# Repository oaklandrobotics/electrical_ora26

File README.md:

# electrical_ora26
Electrical 2026 for Oakland Robotics

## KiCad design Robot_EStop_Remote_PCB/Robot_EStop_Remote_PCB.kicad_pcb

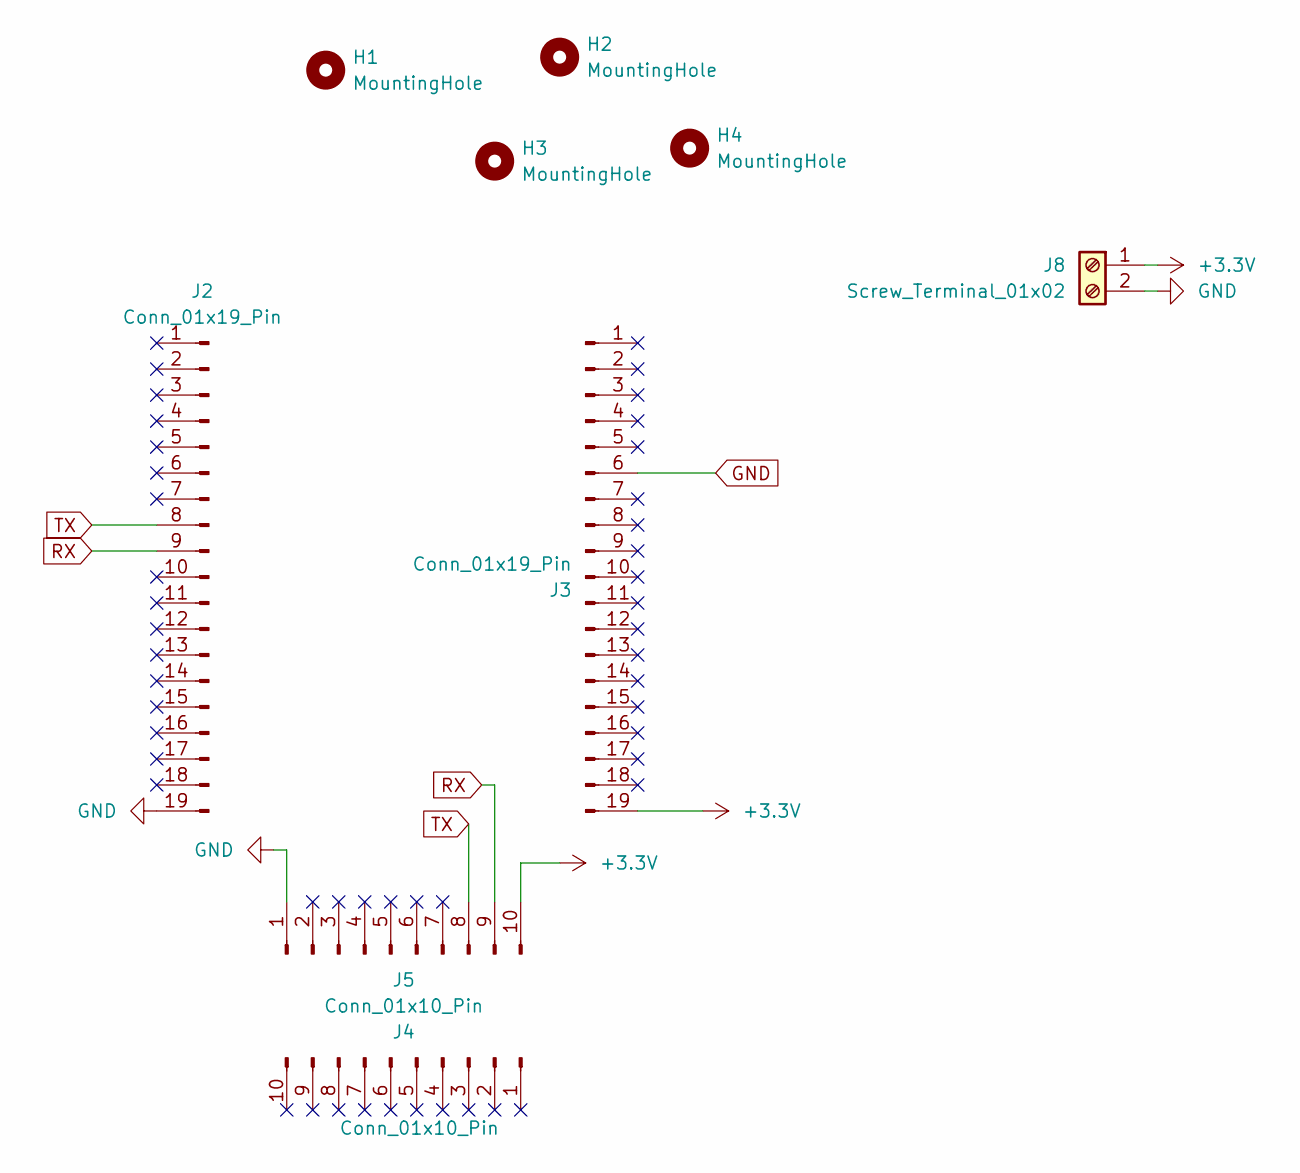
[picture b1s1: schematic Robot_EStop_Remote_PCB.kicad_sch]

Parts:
H1, H2, H3, H4: MountingHole; MountingHole_3.2mm_M3
J2, J3: Conn_01x19_Pin; PinSocket_1x19_P2.54mm_Vertical
J4, J5: Conn_01x10_Pin; PinSocket_1x10_P2.00mm_Vertical
J8: Screw_Terminal_01x02; TerminalBlock_Phoenix_MPT-0,5-2-2.54_1x02_P2.54mm_Horizontal

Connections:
+3.3V: J3.19, J5.10, J8.1
GND: J2.19, J3.6, J5.1, J8.2
RX: J2.9, J5.9
TX: J2.8, J5.8

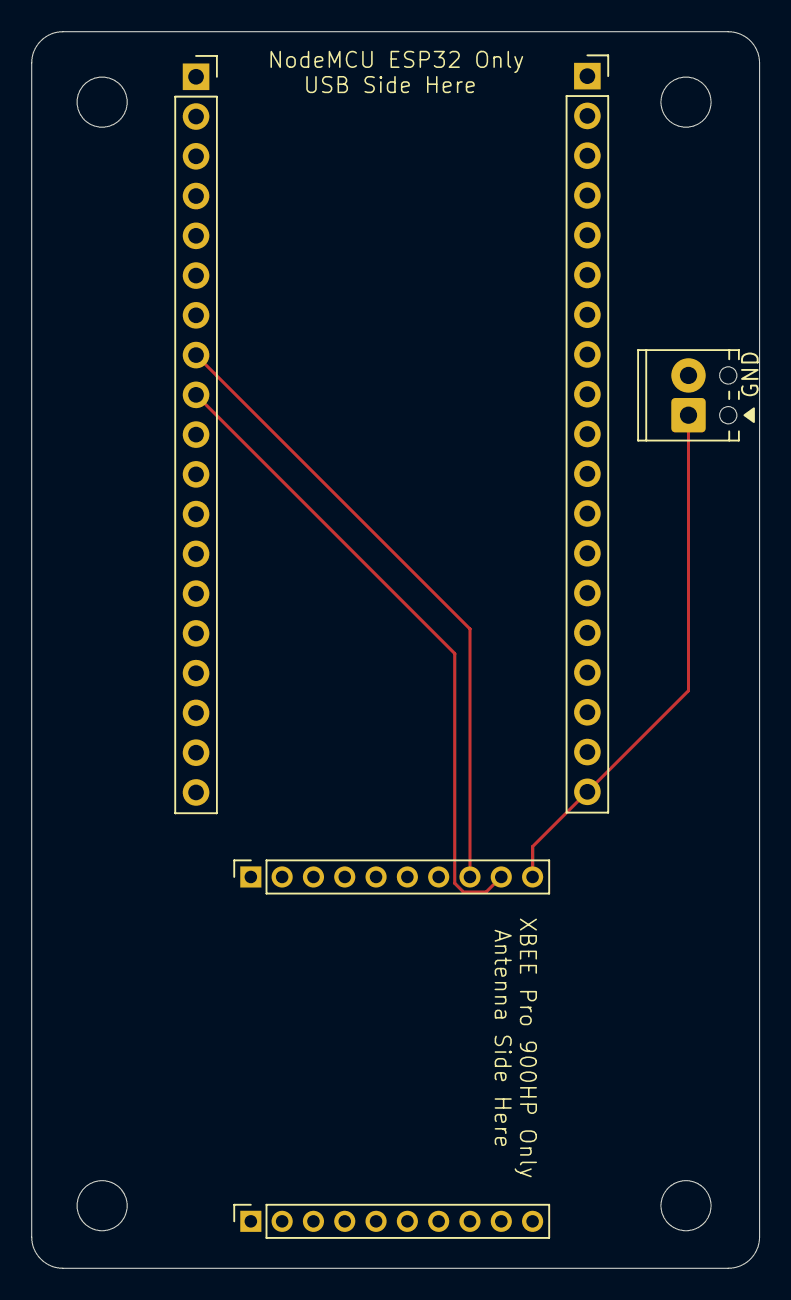
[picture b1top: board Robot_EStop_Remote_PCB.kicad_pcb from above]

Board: 2 copper layers, 46.5 x 79.0 mm, 9 parts (0 on the bottom side), 4 nets.

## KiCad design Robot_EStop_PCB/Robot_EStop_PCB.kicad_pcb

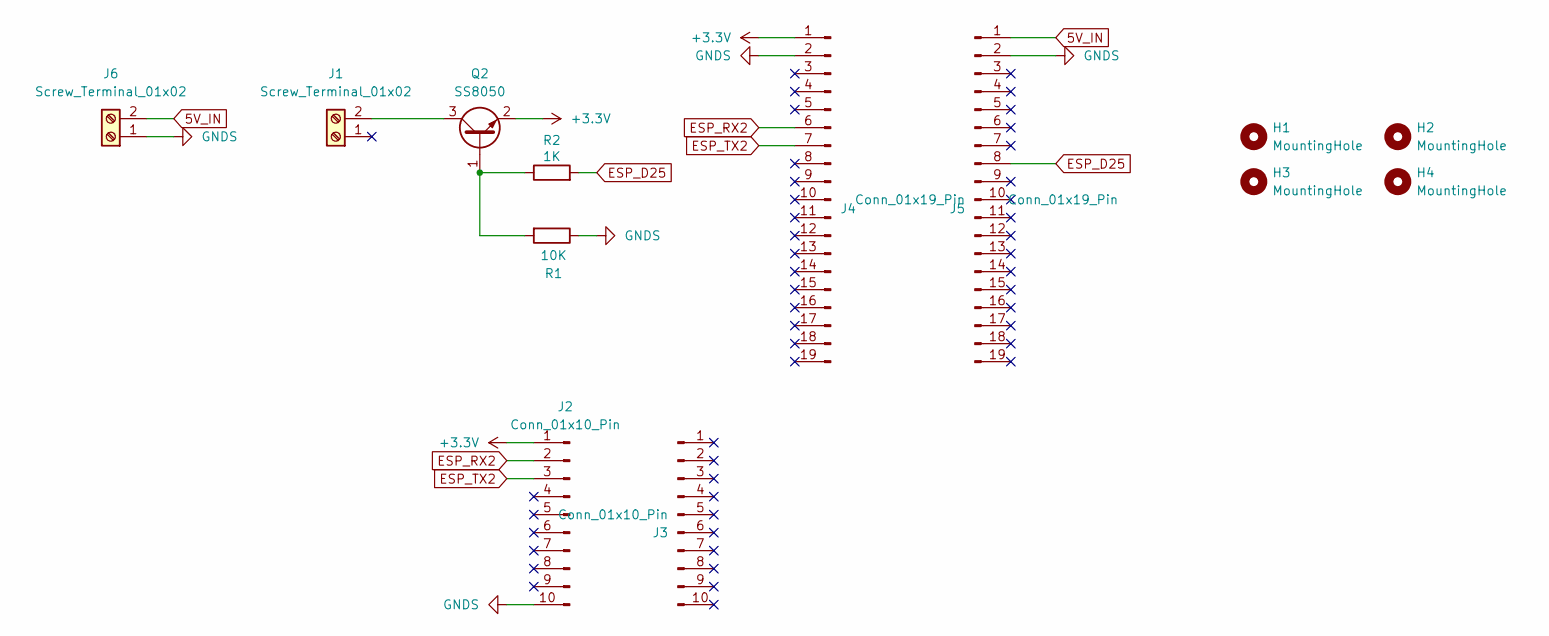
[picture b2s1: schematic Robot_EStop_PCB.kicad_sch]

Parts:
H1, H2, H3, H4: MountingHole; MountingHole_3.2mm_M3
J1, J6: Screw_Terminal_01x02; TerminalBlock_Phoenix_MPT-0,5-2-2.54_1x02_P2.54mm_Horizontal
J2, J3: Conn_01x10_Pin; PinSocket_1x10_P2.00mm_Vertical
J4, J5: Conn_01x19_Pin; PinSocket_1x19_P2.54mm_Vertical
Q2: SS8050; SOT-23
R1: 10K; R_0805_2012Metric_Pad1.20x1.40mm_HandSolder
R2: 1K; R_0805_2012Metric_Pad1.20x1.40mm_HandSolder

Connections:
5V_IN: J5.1, J6.2
+3.3V: J2.1, J4.1, Q2.2 (E)
ESP_D25: J5.8, R2.2
ESP_RX2: J2.2, J4.6
ESP_TX2: J2.3, J4.7
GNDS: J2.10, J4.2, J5.2, J6.1, R1.1
unnamed: J1.2 (Pin_2_2), Q2.3 (C)
unnamed: Q2.1 (B), R1.2, R2.1

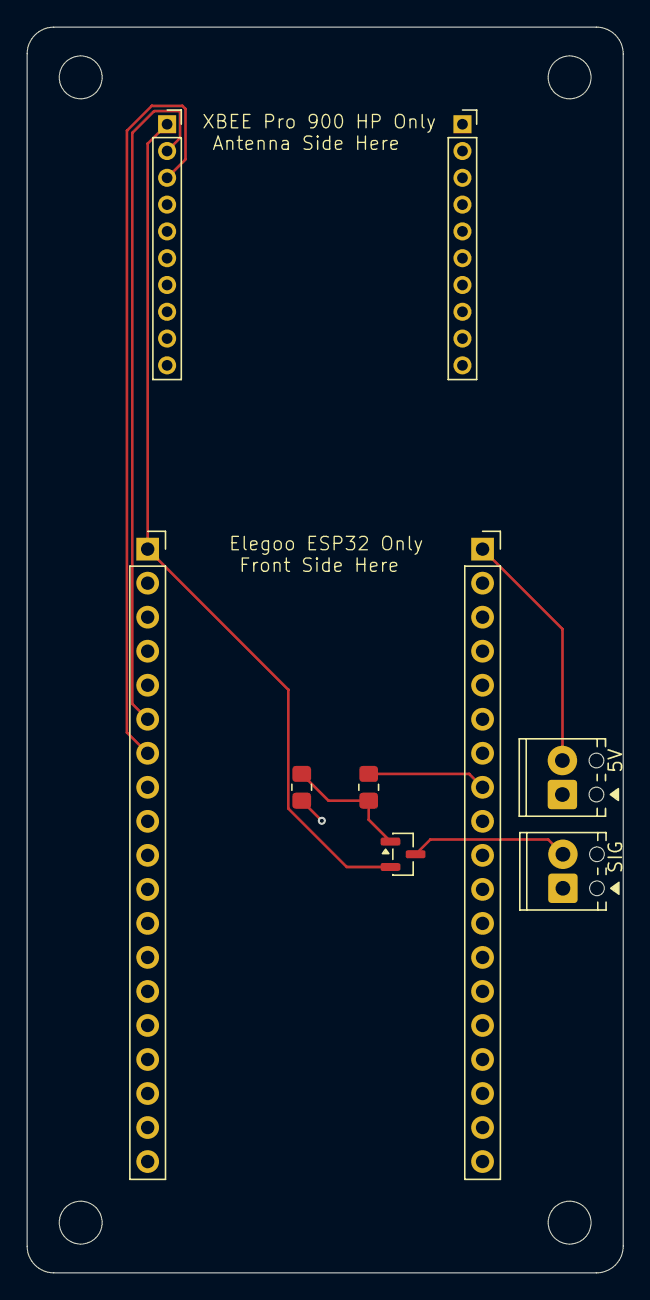
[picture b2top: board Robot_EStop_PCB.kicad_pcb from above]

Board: 2 copper layers, 44.5 x 93.0 mm, 13 parts (0 on the bottom side), 8 nets.
